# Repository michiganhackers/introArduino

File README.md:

Intro to Arduino
============
The support files from the Intro to Arduino and soldering tech talk on Tuesday, November 11 ([presentation can be found here](https://docs.google.com/presentation/d/1E4pHrHvP_do1yQn8vXZZbs_XZ4VM9lmU6rJVV6FsNSU/edit#slide=id.g4b07b791c_350)). In the hardware folder is copies of the Eagle schematic and board layout for the 4x4 LED Arduino shield given to particpants, and in the firmware folder is the library to simplify working with the shield.

The 4x4 LED Arduino shield given to participants. You like it? You should have come!

###How to Install the Library
* Inside of the Arduino IDE, go to Sketch->Import Library->Add Library.
* Choose the *LEDGrid* folder inside of the firmware folder.
* The Arduino IDE handles the rest!
* Be sure to check out the example animation (File->Examples->LEDGrid) if you're unsure how to work with the library, or what to do!

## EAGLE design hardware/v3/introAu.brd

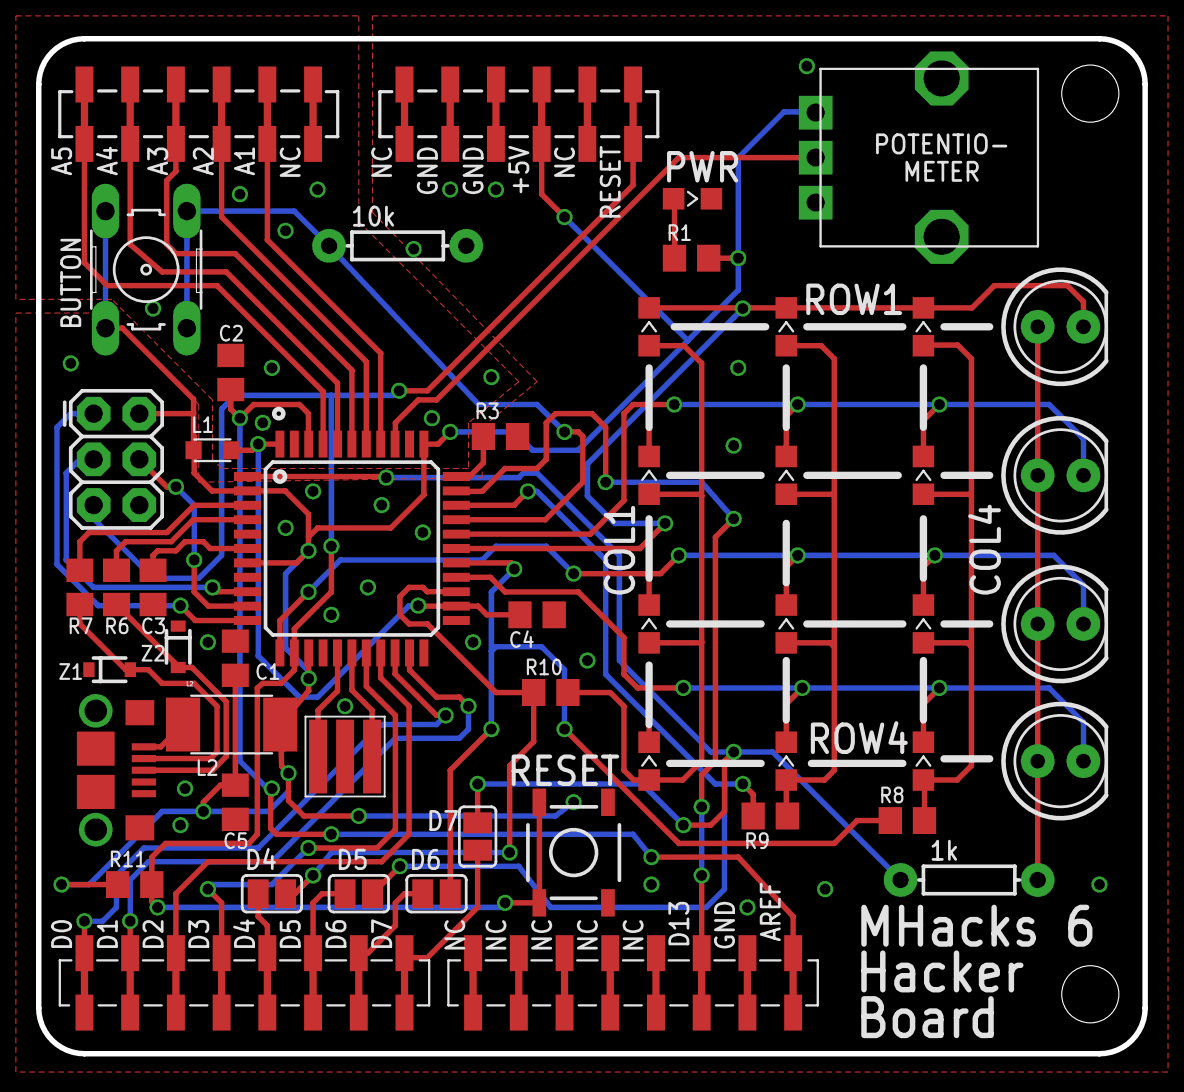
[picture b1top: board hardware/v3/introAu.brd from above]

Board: 2 copper layers, 61.5 x 56.4 mm, 52 parts (1 on the bottom side), 46 nets.

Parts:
C1, C2: 100nF; C0805
C3, C4: 1uF; C0805
C5: 10uF; C0805
D4, D5, D6, D7: SJ
JP1, JP2: 1X06_SMD_STRAIGHT_COMBO
JP3, JP4: 1X08_SMD_COMBINED
JP5: 2X3
L1: WE-CBF_0805(W=3.0)
L2: MF-MSMF050-2; WE-CBF_1812(W=7.3)
LED4, LED9, LED10, LED14: LED5MM
LED17, LED18, LED19, LED20, LED21, LED22, LED23, LED24, LED25, LED26, LED27, LED28: CHIPLED_0805
PWR: CHIPLED_0805
Q1: CERAMIC_RESONATOR_SMD
R1, R8, R9, R10: 1k; R0805
R2: 1k; AXIAL-0.3EZ
R3, R11: 10k; R0805
R5: 10k; AXIAL-0.3EZ
R6, R7: 22; R0805
S1: B3F-10XX
S2: TAC_SWITCHSMD; TACTILE-SWITCH-SMD
U$1: MHACKS6-BIG
U$2: ATMEGA32U4TQFP; SPARKFUN-DIGITALIC_TQFP44
U$3: USB_MICROB_0001LF; USB_MICROB_CHEAPER
U$5: ALPS_POT
Z1, Z2: 3.6V Zener; SOD-323

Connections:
+5V: C1.1, C5.1, JP2.3, JP5.2, L1.1, L2.2, R1.2, R11.2, S1.1, S1.2, U$2.2, U$2.7, U$2.14, U$2.34, U$5.P$1
A1: JP1.2, U$2.37
A2: JP1.3, U$2.38
A3: JP1.4, U$2.39
A4: JP1.5, U$2.40
A5: JP1.6, U$2.41
AREF: C2.1, JP4.1, U$2.42
BUTTON: R5.P$1, S1.3, S1.4, U$2.30
COL1: LED20.A, LED21.A, LED22.A, LED28.A, R10.2
COL2: LED17.A, LED18.A, LED19.A, LED23.A, R9.2
COL3: LED24.A, LED25.A, LED26.A, LED27.A, R8.2
COL4: LED4.A, LED9.A, LED10.A, LED14.A, R2.P$2
D0: JP3.8, U$2.20
D1: JP3.7, U$2.21
D2: JP3.6, U$2.19
D3: JP3.5, U$2.18
D4: D4.1, R10.1, U$2.25
D5: D5.1, R9.1, U$2.31
D6: D6.1, R8.1, U$2.27
D7: D7.1, R2.P$1, U$2.1
D13: JP4.3, U$2.32
GND: C1.2, C2.2, C3.2, C4.2, C5.2, JP2.4, JP2.5, JP4.2, JP5.6, PWR.C, Q1.2, R3.1, R5.P$2, S2.2, U$2.5, U$2.15, U$2.23, U$2.35, U$2.43, U$3.P$5, U$5.P$3, Z1.1, Z2.1
MISO: JP5.1, U$2.11
MOSI: JP5.4, U$2.10
unnamed: L2.1, U$3.P$1
unnamed: Q1.3, U$2.16
unnamed: Q1.1, U$2.17
unnamed: R7.1, U$3.P$2, Z1.2
unnamed: R3.2, U$2.33
unnamed: R6.1, U$3.P$3, Z2.2
unnamed: C4.1, L1.2, U$2.24, U$2.44
unnamed: PWR.A, R1.1
unnamed: D7.2, JP3.1
unnamed: D5.2, JP3.3
unnamed: D6.2, JP3.2
unnamed: D4.2, JP3.4
POT: U$2.36, U$5.P$2
RD+: R6.2, U$2.4
RD-: R7.2, U$2.3
RESET: JP2.1, JP5.5, R11.1, S2.3, S2.4, U$2.13
ROW1: LED4.K, LED23.C, LED27.C, LED28.C, U$2.28
ROW2: LED9.K, LED17.C, LED22.C, LED24.C, U$2.29
ROW3: LED10.K, LED18.C, LED21.C, LED25.C, U$2.12
ROW4: LED14.K, LED19.C, LED20.C, LED26.C, U$2.26
SCK: JP5.3, U$2.9
UCAP: C3.1, U$2.6

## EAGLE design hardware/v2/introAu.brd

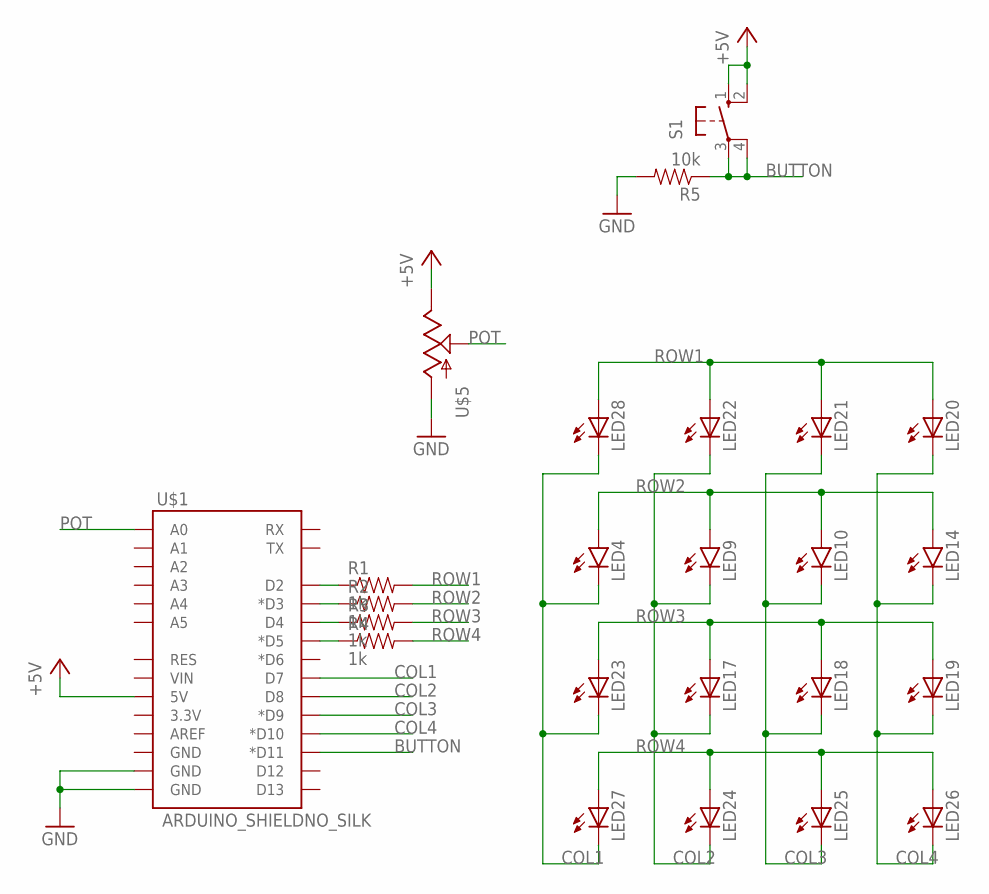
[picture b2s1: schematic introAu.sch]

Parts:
LED4, LED9, LED10, LED14: LED5MM
LED17, LED18, LED19, LED20, LED21, LED22, LED23, LED24, LED25, LED26, LED27, LED28: LEDCHIPLED_0805; CHIPLED_0805
R1, R2, R3, R4: 1k; AXIAL-0.3EZ
R5: 10k; AXIAL-0.3EZ
S1: TACT_BUTTON; B3F-10XX
U$1: ARDUINO_SHIELDNO_SILK; DUEMILANOVE_VIAS
U$5: POT; ALPS_POT

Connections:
+5V: S1.1 (S), S1.2 (S1), U$1.5V, U$5.P$1 (E)
BUTTON: R5.P$1 (1), S1.3, S1.4 (P1), U$1.D11 (*D11)
COL1: LED4.K (C), LED23.C, LED27.C, LED28.C, U$1.D7
COL2: LED9.K (C), LED17.C, LED22.C, LED24.C, U$1.D8
COL3: LED10.K (C), LED18.C, LED21.C, LED25.C, U$1.D9 (*D9)
COL4: LED14.K (C), LED19.C, LED20.C, LED26.C, U$1.D10 (*D10)
GND: R5.P$2 (2), U$1.GND@0 (GND), U$1.GND@1 (GND), U$5.P$3 (A)
unnamed: R1.P$1 (1), U$1.D2
unnamed: R2.P$1 (1), U$1.D3 (*D3)
unnamed: R3.P$1 (1), U$1.D4
unnamed: R4.P$1 (1), U$1.D5 (*D5)
POT: U$1.A0, U$5.P$2 (S)
ROW1: LED20.A, LED21.A, LED22.A, LED28.A, R1.P$2 (2)
ROW2: LED4.A, LED9.A, LED10.A, LED14.A, R2.P$2 (2)
ROW3: LED17.A, LED18.A, LED19.A, LED23.A, R3.P$2 (2)
ROW4: LED24.A, LED25.A, LED26.A, LED27.A, R4.P$2 (2)

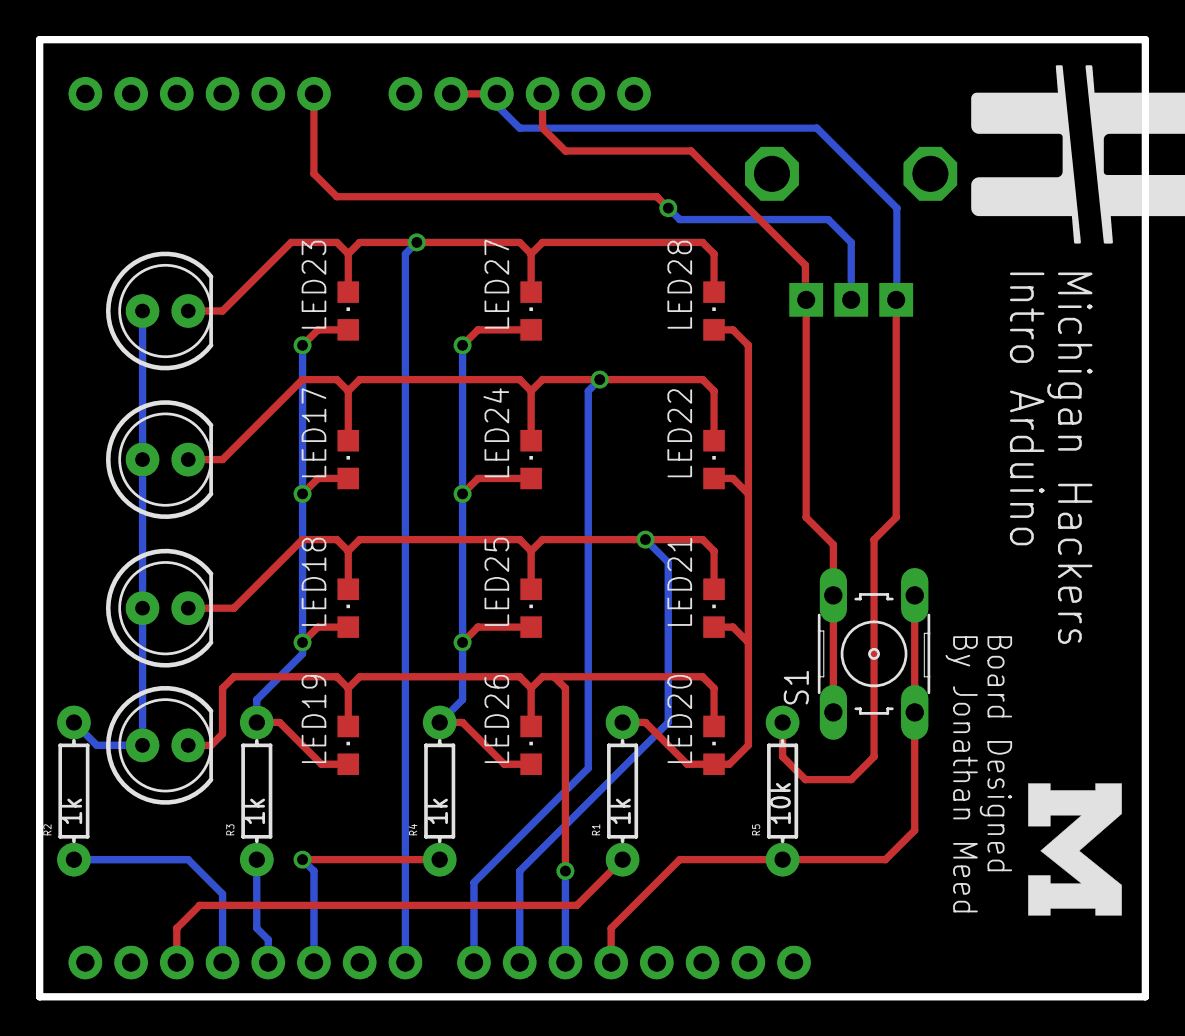
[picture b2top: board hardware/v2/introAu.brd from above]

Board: 2 copper layers, 61.4 x 53.2 mm, 26 parts (0 on the bottom side), 16 nets.

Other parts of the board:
U$2: SMALL-M
U$3: SMALL-MH

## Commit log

2014-11-08 Updated README, removed unneccessary ledGrid.zip for installing in Arduino IDE as a library
2014-11-11 added basic animation
2015-05-26 Started new revision, with different features
2015-05-28 Added potentiometer, button, surface mount LEDs to v2
2015-08-04 Merged in Leonardo onboard
2015-08-14 Added v3 of board
2015-08-16 Trying to make this perfect. Too many changes to count.
2015-08-18 Made more critical changes
2015-08-19 Fiddled with GND polygons

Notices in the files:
parts and their libraries:
SparkFun-Boards: Licensing: Creative Commons ShareAlike 4.0 International - https://creativecommons.org/licenses/by-sa/4.0
SparkFun-Electromechanical: Licensing: CC v3.0 Share-Alike You are welcome to use this library for commercial purposes.
